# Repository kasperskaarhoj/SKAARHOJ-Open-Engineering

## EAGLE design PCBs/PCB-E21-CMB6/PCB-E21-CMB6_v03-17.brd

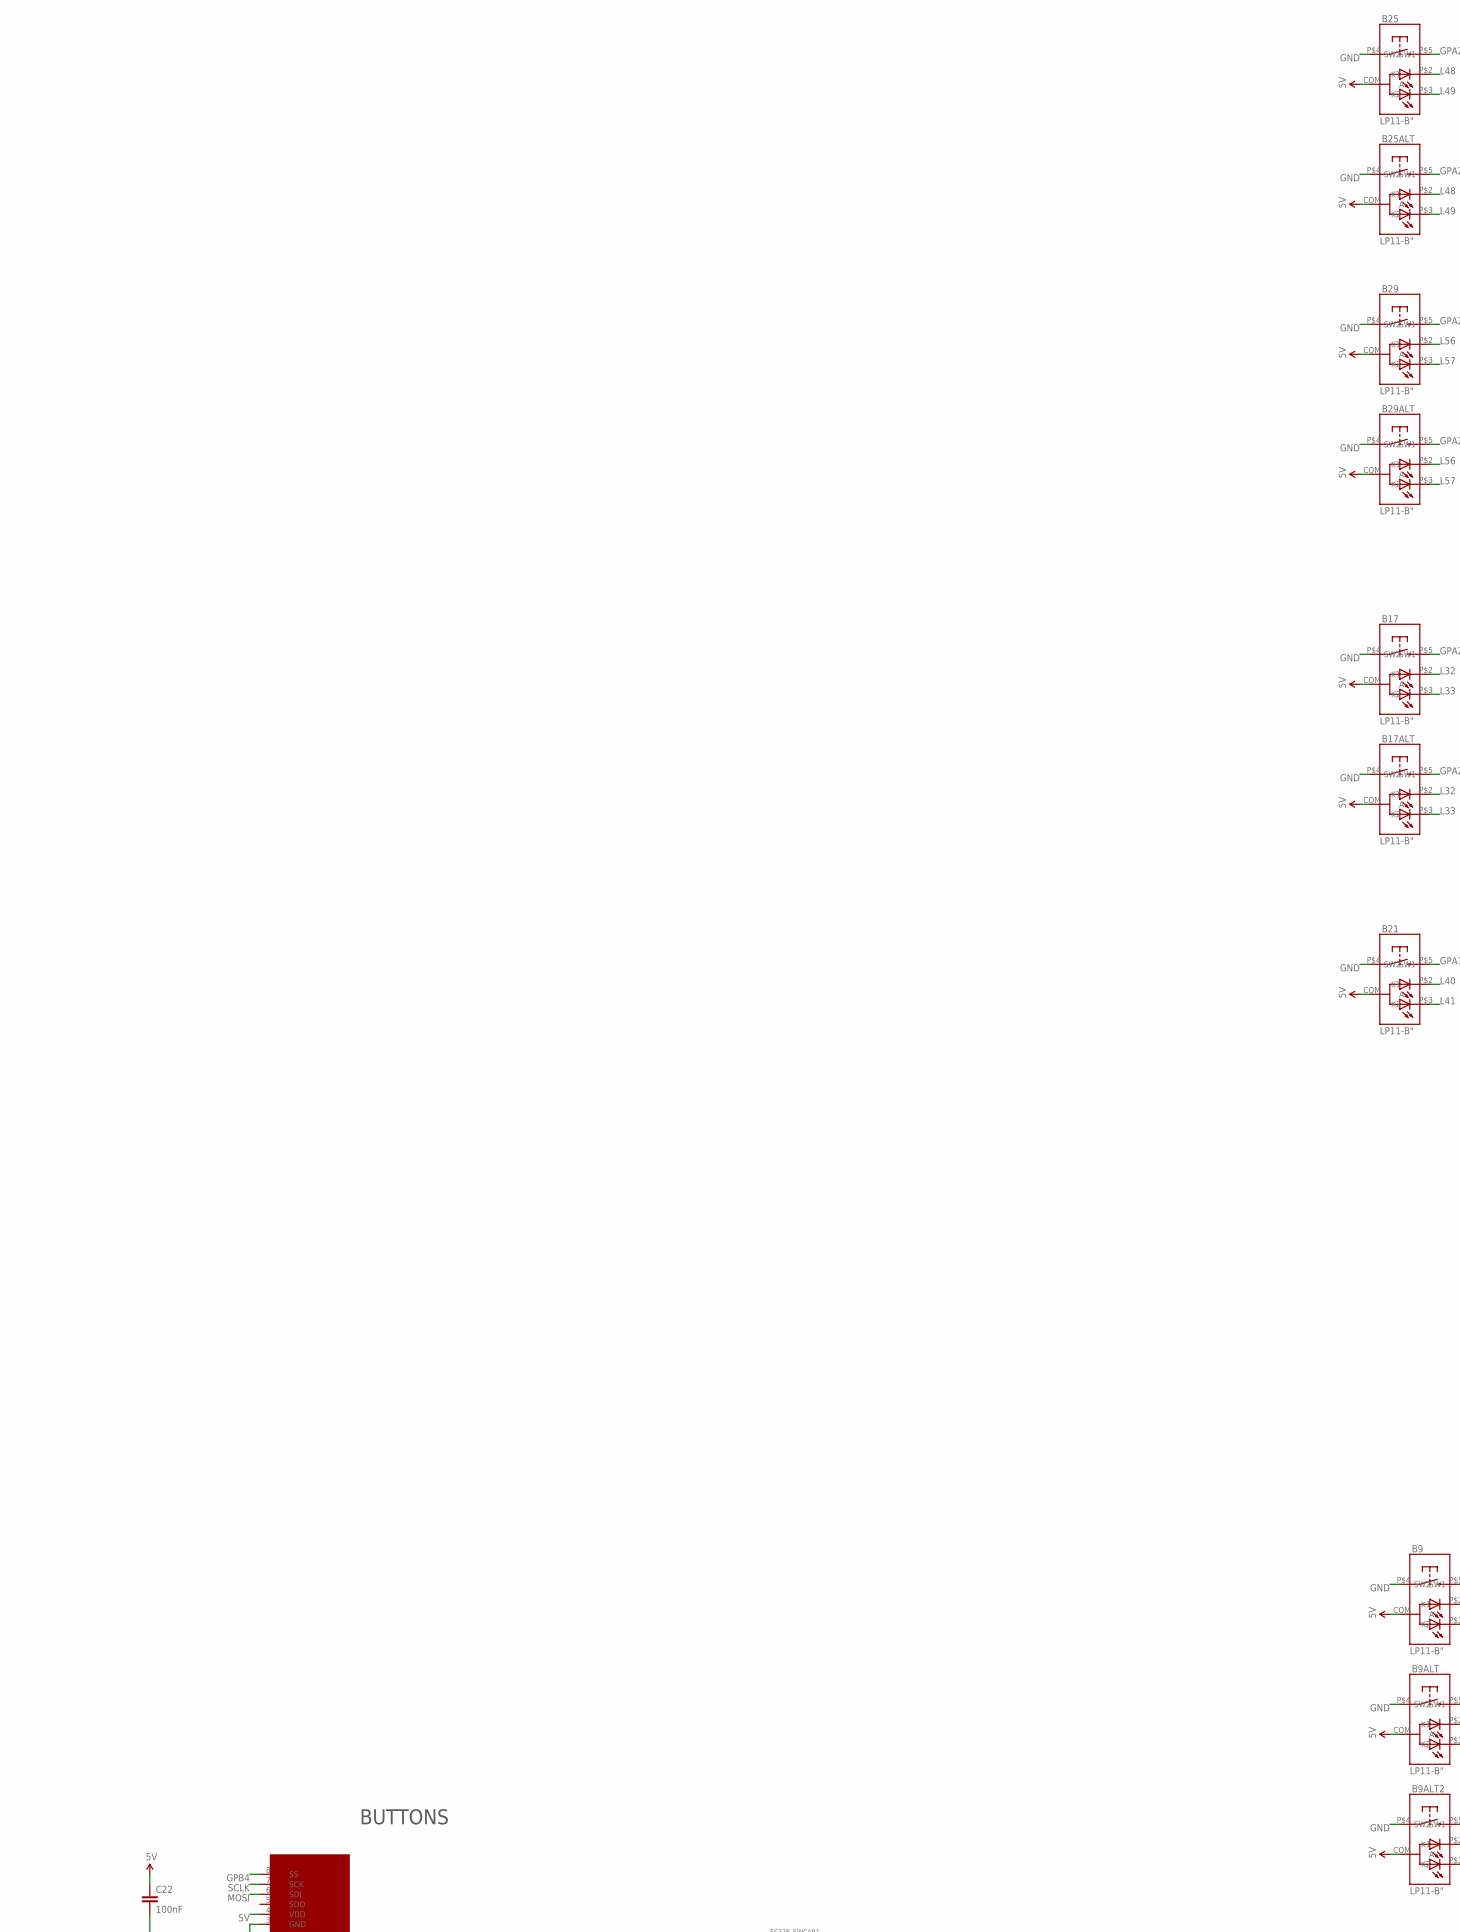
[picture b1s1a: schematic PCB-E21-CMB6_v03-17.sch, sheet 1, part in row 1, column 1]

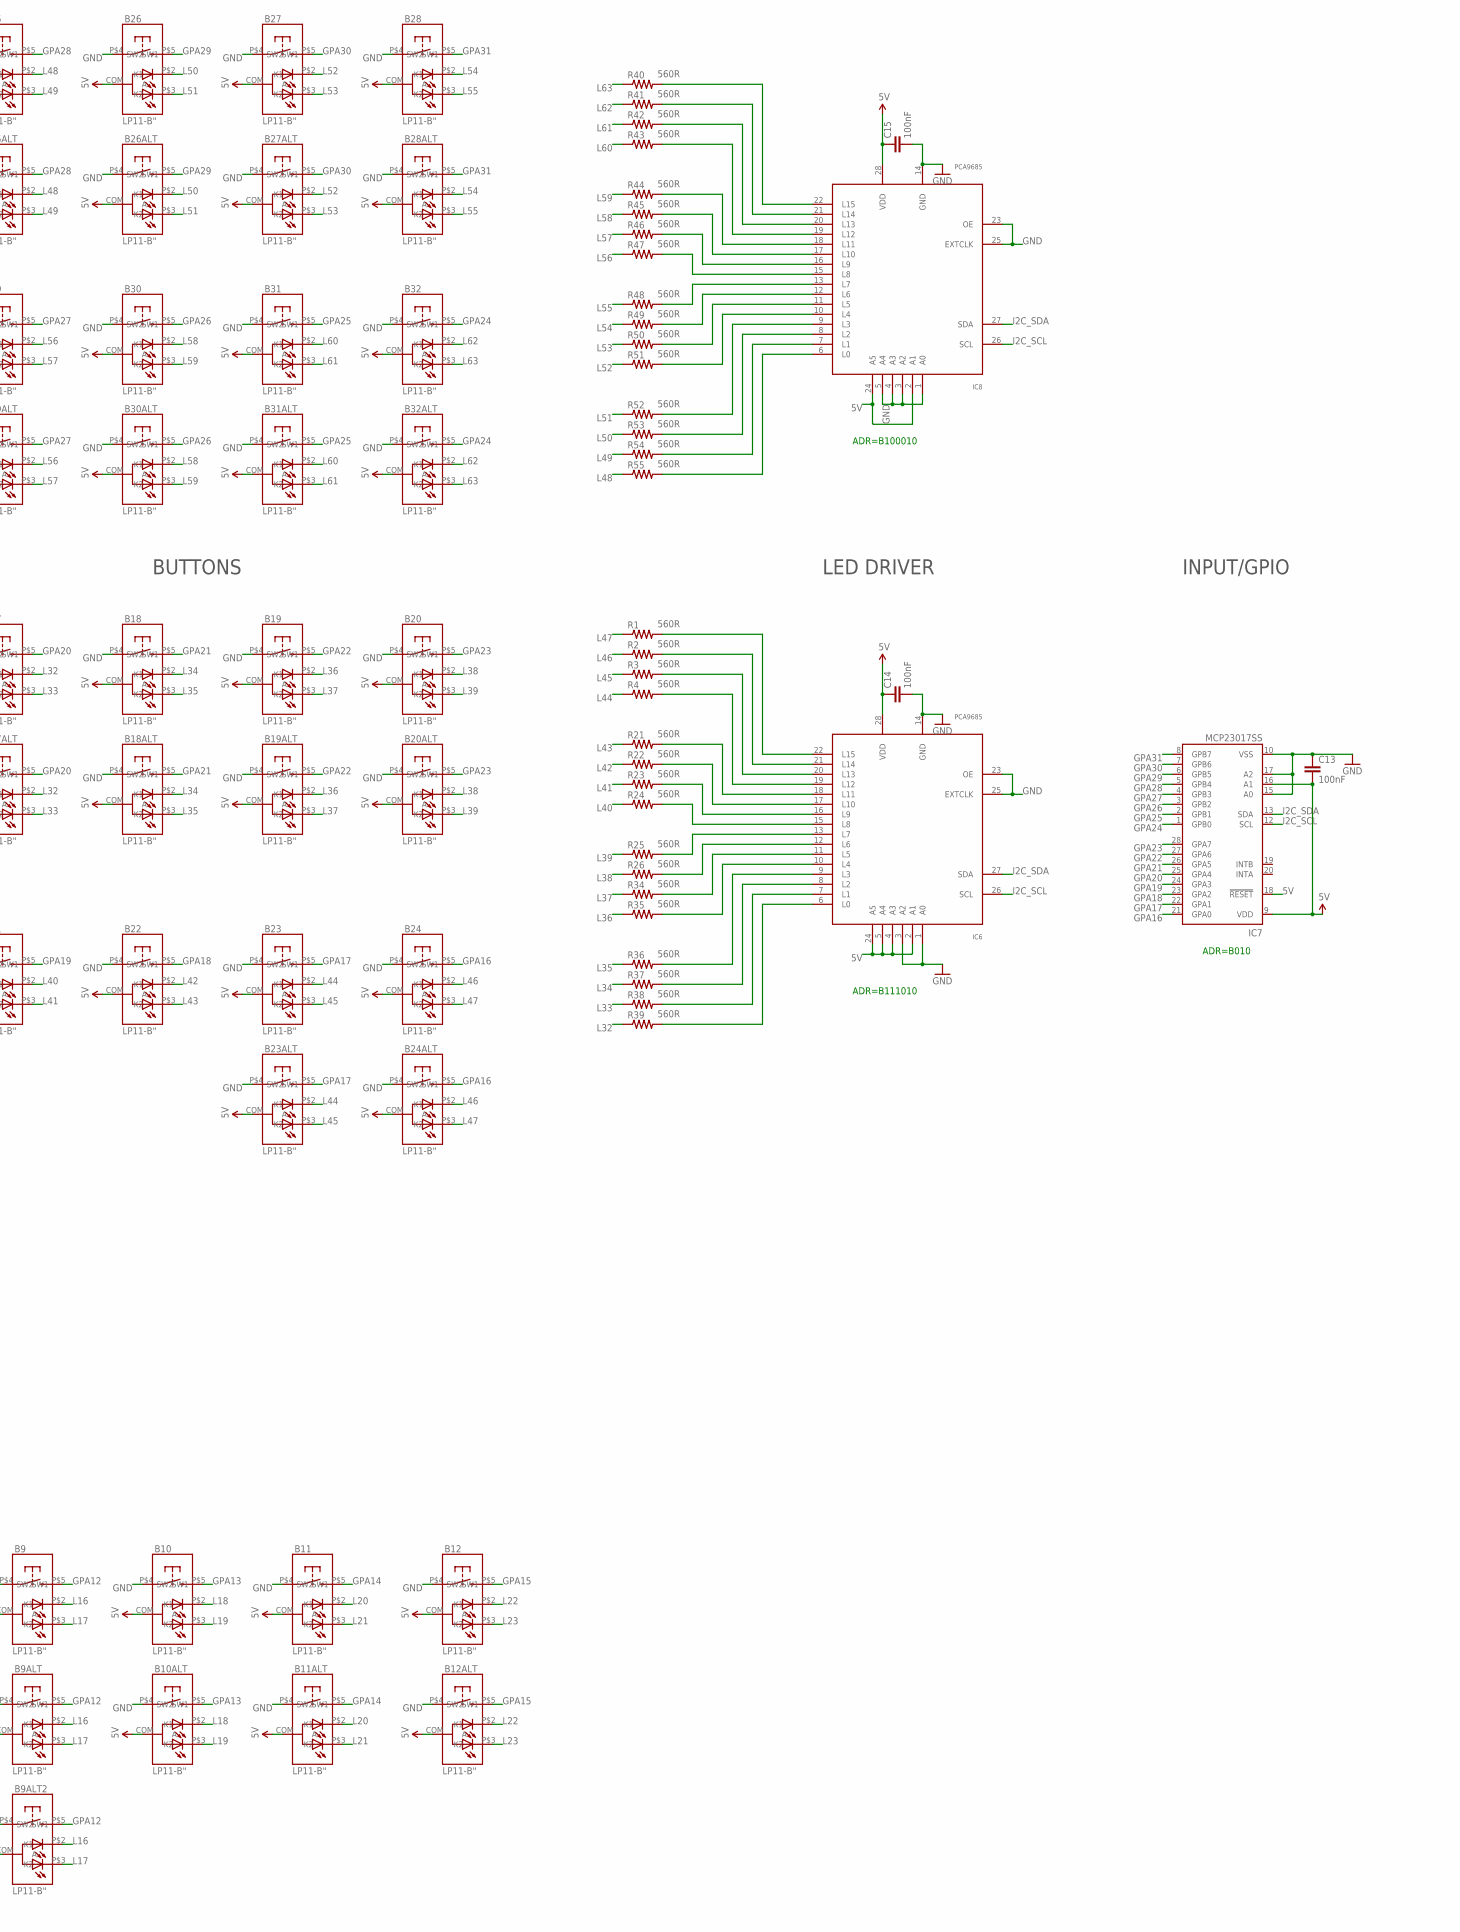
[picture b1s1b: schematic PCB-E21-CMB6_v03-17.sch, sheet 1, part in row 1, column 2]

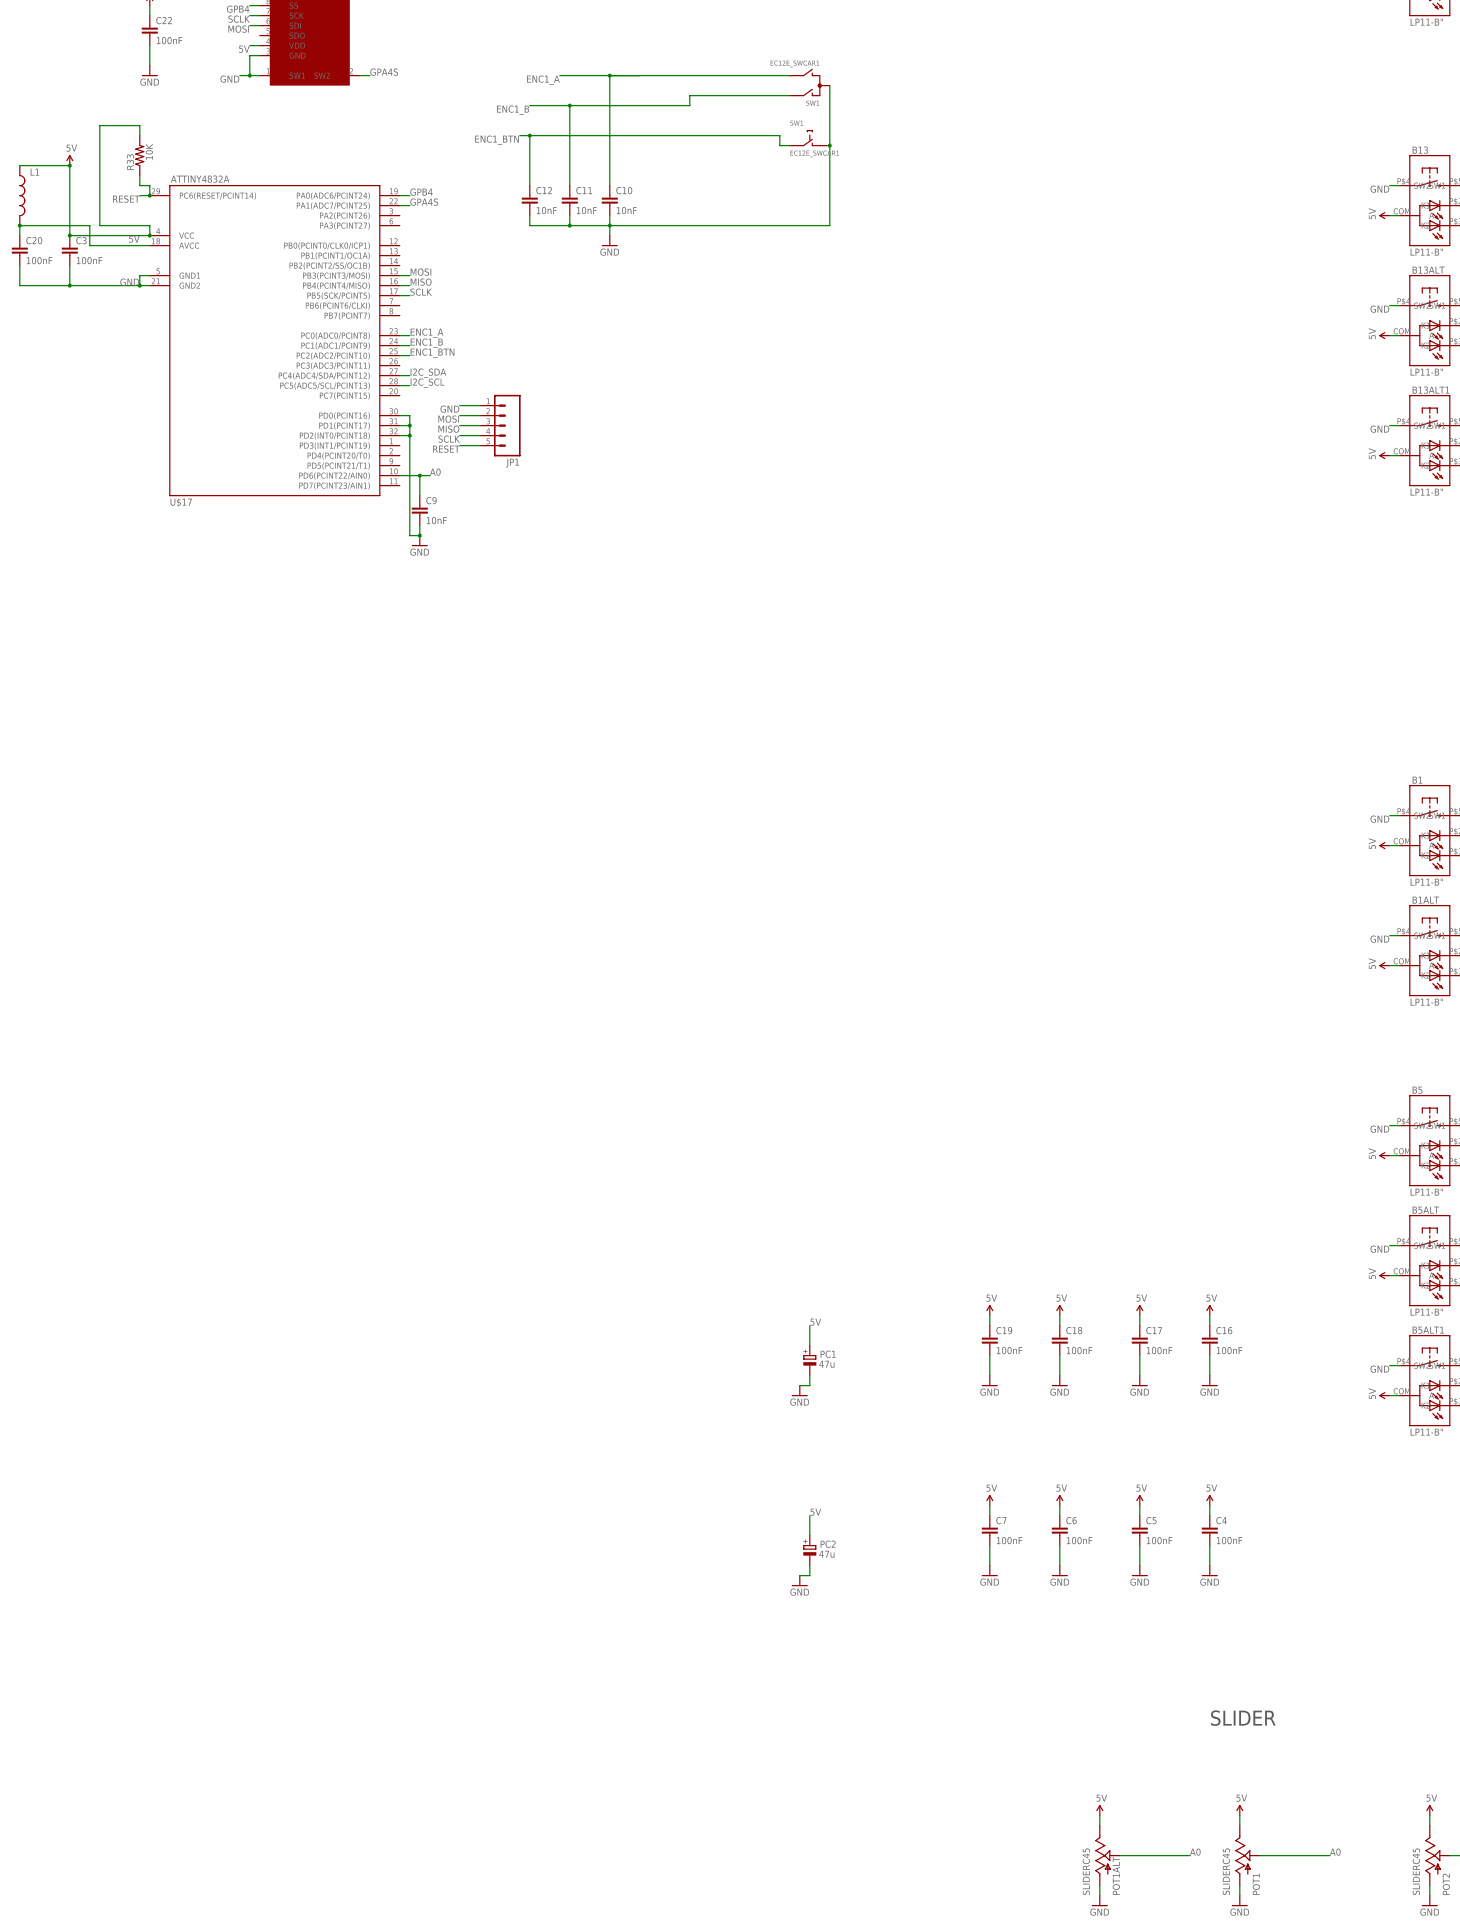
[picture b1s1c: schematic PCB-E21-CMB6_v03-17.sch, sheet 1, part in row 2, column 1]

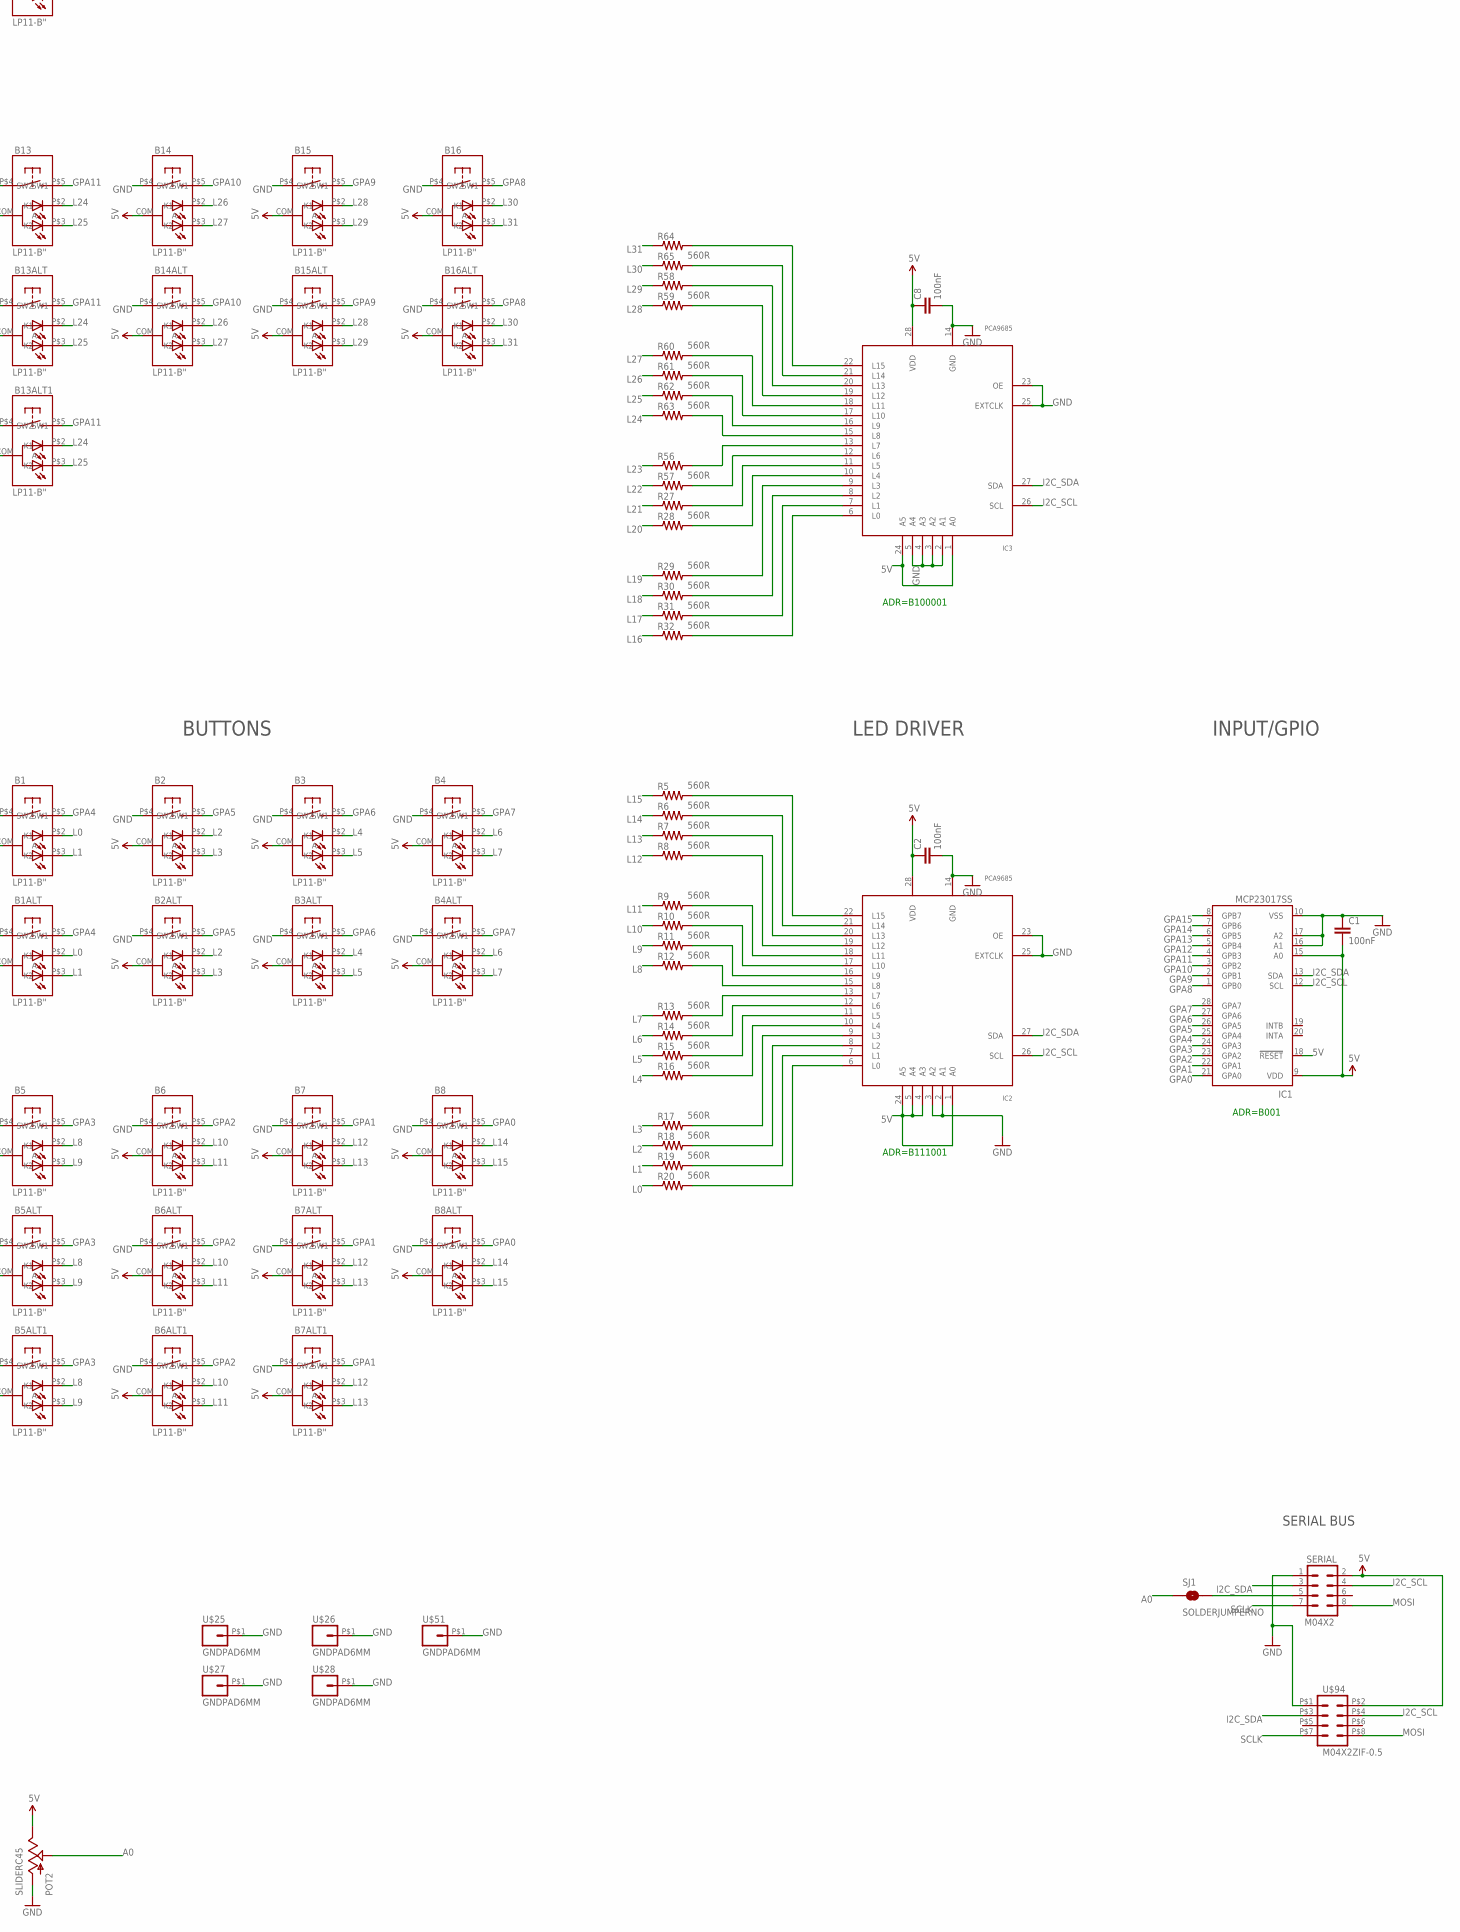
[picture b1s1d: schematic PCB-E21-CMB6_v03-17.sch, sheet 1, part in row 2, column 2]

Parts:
B1, B1ALT, B2, B2ALT, B3, B3ALT, B4, B4ALT, B5, B5ALT, B5ALT1, B6, B6ALT, B6ALT1, B7, B7ALT, B7ALT1, B8, B8ALT, B9, B9ALT, B9ALT2, B10, B10ALT, B11, B11ALT, B12, B12ALT, B13, B13ALT, B13ALT1, B14, B14ALT, B15, B15ALT, B16, B16ALT, B17, B17ALT, B18, B18ALT, B19, B19ALT, B20, B20ALT, B21, B22, B23, B23ALT, B24, B24ALT, B25, B25ALT, B26, B26ALT, B27, B27ALT, B28, B28ALT, B29, B29ALT, B30, B30ALT, B31, B31ALT, B32, B32ALT: LP11-B"; LP11
C1, C2, C3, C4, C5, C6, C7, C8, C13, C14, C15, C16, C17, C18, C19, C20, C22: 100nF; 0603-CAP
C9, C10, C11, C12: 10nF; 0603-CAP
IC1, IC7: MCP23017SS; SSOP28; MPN MCP23017-E/SS
IC2, IC3, IC6, IC8: PCA9685; TSSOP28
JP1: M051.27MM; 1X05-1.27MM
L1: INDUCTOR0805; 0805
PC1, PC2: 47u; PANASONIC_D
POT1, POT1ALT, POT2: SLIDERC45; SLIDER45-CAR1
R1, R2, R3, R4, R5, R6, R7, R8, R9, R10, R11, R12, R13, R14, R15, R16, R17, R18, R19, R20, R21, R22, R23, R24, R25, R26, R27, R28, R29, R30, R31, R32, R34, R35, R36, R37, R38, R39, R40, R41, R42, R43, R44, R45, R46, R47, R48, R49, R50, R51, R52, R53, R54, R55, R56, R57, R58, R59, R60, R61, R62, R63, R64, R65: 560R; 0603-RES
R33: 10K; 0603-RES
SERIAL: M04X2; 2X4
SJ1: SOLDERJUMPERNO; SJ_2S-NO
SSW1: SMART_SWITCHSMART_SWITCH_8PIN; SMART_SWITCH
SW1: EC12E_SWCAR1; ALPS_EC12E_SW-CAR1
U$17: ATTINY4832A; TQFP32-08
U$25, U$26, U$27, U$28, U$51: GNDPAD6MM; 3.2MMPAD6MM
U$94: M04X2ZIF-0.5; ZIP-8-0.5

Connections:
5V: B1.COM (A), B1ALT.COM (A), B2.COM (A), B2ALT.COM (A), B3.COM (A), B3ALT.COM (A), B4.COM (A), B4ALT.COM (A), B5.COM (A), B5ALT.COM (A), B5ALT1.COM (A), B6.COM (A), B6ALT.COM (A), B6ALT1.COM (A), B7.COM (A), B7ALT.COM (A), B7ALT1.COM (A), B8.COM (A), B8ALT.COM (A), B9.COM (A), B9ALT.COM (A), B9ALT2.COM (A), B10.COM (A), B10ALT.COM (A), B11.COM (A), B11ALT.COM (A), B12.COM (A), B12ALT.COM (A), B13.COM (A), B13ALT.COM (A), B13ALT1.COM (A), B14.COM (A), B14ALT.COM (A), B15.COM (A), B15ALT.COM (A), B16.COM (A), B16ALT.COM (A), B17.COM (A), B17ALT.COM (A), B18.COM (A), B18ALT.COM (A), B19.COM (A), B19ALT.COM (A), B20.COM (A), B20ALT.COM (A), B21.COM (A), B22.COM (A), B23.COM (A), B23ALT.COM (A), B24.COM (A), B24ALT.COM (A), B25.COM (A), B25ALT.COM (A), B26.COM (A), B26ALT.COM (A), B27.COM (A), B27ALT.COM (A), B28.COM (A), B28ALT.COM (A), B29.COM (A), B29ALT.COM (A), B30.COM (A), B30ALT.COM (A), B31.COM (A), B31ALT.COM (A), B32.COM (A), B32ALT.COM (A), C1.2, C2.1, C3.1, C4.1, C5.1, C6.1, C7.1, C8.1, C13.2, C14.1, C15.1, C16.1, C17.1, C18.1, C19.1, C22.1, IC1.9 (VDD), IC1.15 (A0), IC1.18 (!RESET), IC2.1 (A0), IC2.4 (A3), IC2.5 (A4), IC2.24 (A5), IC2.28 (VDD), IC3.1 (A0), IC3.24 (A5), IC3.28 (VDD), IC6.2 (A1), IC6.4 (A3), IC6.5 (A4), IC6.24 (A5), IC6.28 (VDD), IC7.9 (VDD), IC7.16 (A1), IC7.18 (!RESET), IC8.2 (A1), IC8.24 (A5), IC8.28 (VDD), L1.1, PC1.+, PC2.+, POT1.1 (E), POT1ALT.1 (E), POT2.1 (E), R33.2, SERIAL.2, SSW1.4 (VDD), U$17.4 (VCC), U$94.P$2 (2)
A0: C9.1, POT1.2A (S), POT1ALT.2A (S), POT2.2A (S), SJ1.1, U$17.10 (PD6(PCINT22/AIN0))
ENC1_A: C10.1, SW1.B, U$17.23 (PC0(ADC0/PCINT8))
ENC1_B: C11.1, SW1.A, U$17.24 (PC1(ADC1/PCINT9))
ENC1_BTN: C12.1, SW1.E (2), U$17.25 (PC2(ADC2/PCINT10))
GND: B1.P$4 (SW1), B1ALT.P$4 (SW1), B2.P$4 (SW1), B2ALT.P$4 (SW1), B3.P$4 (SW1), B3ALT.P$4 (SW1), B4.P$4 (SW1), B4ALT.P$4 (SW1), B5.P$4 (SW1), B5ALT.P$4 (SW1), B5ALT1.P$4 (SW1), B6.P$4 (SW1), B6ALT.P$4 (SW1), B6ALT1.P$4 (SW1), B7.P$4 (SW1), B7ALT.P$4 (SW1), B7ALT1.P$4 (SW1), B8.P$4 (SW1), B8ALT.P$4 (SW1), B9.P$4 (SW1), B9ALT.P$4 (SW1), B9ALT2.P$4 (SW1), B10.P$4 (SW1), B10ALT.P$4 (SW1), B11.P$4 (SW1), B11ALT.P$4 (SW1), B12.P$4 (SW1), B12ALT.P$4 (SW1), B13.P$4 (SW1), B13ALT.P$4 (SW1), B13ALT1.P$4 (SW1), B14.P$4 (SW1), B14ALT.P$4 (SW1), B15.P$4 (SW1), B15ALT.P$4 (SW1), B16.P$4 (SW1), B16ALT.P$4 (SW1), B17.P$4 (SW1), B17ALT.P$4 (SW1), B18.P$4 (SW1), B18ALT.P$4 (SW1), B19.P$4 (SW1), B19ALT.P$4 (SW1), B20.P$4 (SW1), B20ALT.P$4 (SW1), B21.P$4 (SW1), B22.P$4 (SW1), B23.P$4 (SW1), B23ALT.P$4 (SW1), B24.P$4 (SW1), B24ALT.P$4 (SW1), B25.P$4 (SW1), B25ALT.P$4 (SW1), B26.P$4 (SW1), B26ALT.P$4 (SW1), B27.P$4 (SW1), B27ALT.P$4 (SW1), B28.P$4 (SW1), B28ALT.P$4 (SW1), B29.P$4 (SW1), B29ALT.P$4 (SW1), B30.P$4 (SW1), B30ALT.P$4 (SW1), B31.P$4 (SW1), B31ALT.P$4 (SW1), B32.P$4 (SW1), B32ALT.P$4 (SW1), C1.1, C2.2, C3.2, C4.2, C5.2, C6.2, C7.2, C8.2, C9.2, C10.2, C11.2, C12.2, C13.1, C14.2, C15.2, C16.2, C17.2, C18.2, C19.2, C20.2, C22.2, IC1.10 (VSS), IC1.16 (A1), IC1.17 (A2), IC2.2 (A1), IC2.3 (A2), IC2.14 (GND), IC2.23 (OE), IC2.25 (EXTCLK), IC3.2 (A1), IC3.3 (A2), IC3.4 (A3), IC3.5 (A4), IC3.14 (GND), IC3.23 (OE), IC3.25 (EXTCLK), IC6.1 (A0), IC6.3 (A2), IC6.14 (GND), IC6.23 (OE), IC6.25 (EXTCLK), IC7.10 (VSS), IC7.15 (A0), IC7.17 (A2), IC8.1 (A0), IC8.3 (A2), IC8.4 (A3), IC8.5 (A4), IC8.14 (GND), IC8.23 (OE), IC8.25 (EXTCLK), JP1.1, PC1.-, PC2.-, POT1.3 (A), POT1ALT.3 (A), POT2.3 (A), SERIAL.1, SSW1.1 (SW1), SSW1.3 (GND), SW1.C, SW1.D (1), U$17.5 (GND1), U$17.21 (GND2), U$17.30 (PD0(PCINT16)), U$17.31 (PD1(PCINT17)), U$17.32 (PD2(INT0/PCINT18)), U$25.P$1, U$26.P$1, U$27.P$1, U$28.P$1, U$51.P$1, U$94.P$1 (1)
GPA0: B8.P$5 (SW2), B8ALT.P$5 (SW2), IC1.21 (GPA0)
GPA1: B7.P$5 (SW2), B7ALT.P$5 (SW2), B7ALT1.P$5 (SW2), IC1.22 (GPA1)
GPA2: B6.P$5 (SW2), B6ALT.P$5 (SW2), B6ALT1.P$5 (SW2), IC1.23 (GPA2)
GPA3: B5.P$5 (SW2), B5ALT.P$5 (SW2), B5ALT1.P$5 (SW2), IC1.24 (GPA3)
GPA4: B1.P$5 (SW2), B1ALT.P$5 (SW2), IC1.25 (GPA4)
GPA4S: SSW1.2 (SW2), U$17.22 (PA1(ADC7/PCINT25))
GPA5: B2.P$5 (SW2), B2ALT.P$5 (SW2), IC1.26 (GPA5)
GPA6: B3.P$5 (SW2), B3ALT.P$5 (SW2), IC1.27 (GPA6)
GPA7: B4.P$5 (SW2), B4ALT.P$5 (SW2), IC1.28 (GPA7)
GPA8: B16.P$5 (SW2), B16ALT.P$5 (SW2), IC1.1 (GPB0)
GPA9: B15.P$5 (SW2), B15ALT.P$5 (SW2), IC1.2 (GPB1)
GPA10: B14.P$5 (SW2), B14ALT.P$5 (SW2), IC1.3 (GPB2)
GPA11: B13.P$5 (SW2), B13ALT.P$5 (SW2), B13ALT1.P$5 (SW2), IC1.4 (GPB3)
GPA12: B9.P$5 (SW2), B9ALT.P$5 (SW2), B9ALT2.P$5 (SW2), IC1.5 (GPB4)
GPA13: B10.P$5 (SW2), B10ALT.P$5 (SW2), IC1.6 (GPB5)
GPA14: B11.P$5 (SW2), B11ALT.P$5 (SW2), IC1.7 (GPB6)
GPA15: B12.P$5 (SW2), B12ALT.P$5 (SW2), IC1.8 (GPB7)
GPA16: B24.P$5 (SW2), B24ALT.P$5 (SW2), IC7.21 (GPA0)
GPA17: B23.P$5 (SW2), B23ALT.P$5 (SW2), IC7.22 (GPA1)
GPA18: B22.P$5 (SW2), IC7.23 (GPA2)
GPA19: B21.P$5 (SW2), IC7.24 (GPA3)
GPA20: B17.P$5 (SW2), B17ALT.P$5 (SW2), IC7.25 (GPA4)
GPA21: B18.P$5 (SW2), B18ALT.P$5 (SW2), IC7.26 (GPA5)
GPA22: B19.P$5 (SW2), B19ALT.P$5 (SW2), IC7.27 (GPA6)
GPA23: B20.P$5 (SW2), B20ALT.P$5 (SW2), IC7.28 (GPA7)
GPA24: B32.P$5 (SW2), B32ALT.P$5 (SW2), IC7.1 (GPB0)
GPA25: B31.P$5 (SW2), B31ALT.P$5 (SW2), IC7.2 (GPB1)
GPA26: B30.P$5 (SW2), B30ALT.P$5 (SW2), IC7.3 (GPB2)
GPA27: B29.P$5 (SW2), B29ALT.P$5 (SW2), IC7.4 (GPB3)
GPA28: B25.P$5 (SW2), B25ALT.P$5 (SW2), IC7.5 (GPB4)
GPA29: B26.P$5 (SW2), B26ALT.P$5 (SW2), IC7.6 (GPB5)
GPA30: B27.P$5 (SW2), B27ALT.P$5 (SW2), IC7.7 (GPB6)
GPA31: B28.P$5 (SW2), B28ALT.P$5 (SW2), IC7.8 (GPB7)
GPB4: SSW1.8 (SS), U$17.19 (PA0(ADC6/PCINT24))
I2C_SCL: IC1.12 (SCL), IC2.26 (SCL), IC3.26 (SCL), IC6.26 (SCL), IC7.12 (SCL), IC8.26 (SCL), SERIAL.4, U$17.28 (PC5(ADC5/SCL/PCINT13)), U$94.P$4 (4)
I2C_SDA: IC1.13 (SDA), IC2.27 (SDA), IC3.27 (SDA), IC6.27 (SDA), IC7.13 (SDA), IC8.27 (SDA), SERIAL.3, U$17.27 (PC4(ADC4/SDA/PCINT12)), U$94.P$3 (3)
L0: B1.P$2 (K1), B1ALT.P$2 (K1), R20.1
L1: B1.P$3 (K2), B1ALT.P$3 (K2), R19.1
L2: B2.P$2 (K1), B2ALT.P$2 (K1), R18.1
L3: B2.P$3 (K2), B2ALT.P$3 (K2), R17.1
L4: B3.P$2 (K1), B3ALT.P$2 (K1), R16.1
L5: B3.P$3 (K2), B3ALT.P$3 (K2), R15.1
L6: B4.P$2 (K1), B4ALT.P$2 (K1), R14.1
L7: B4.P$3 (K2), B4ALT.P$3 (K2), R13.1
L8: B5.P$2 (K1), B5ALT.P$2 (K1), B5ALT1.P$2 (K1), R12.1
L9: B5.P$3 (K2), B5ALT.P$3 (K2), B5ALT1.P$3 (K2), R11.1
L10: B6.P$2 (K1), B6ALT.P$2 (K1), B6ALT1.P$2 (K1), R10.1
L11: B6.P$3 (K2), B6ALT.P$3 (K2), B6ALT1.P$3 (K2), R9.1
L12: B7.P$2 (K1), B7ALT.P$2 (K1), B7ALT1.P$2 (K1), R8.1
L13: B7.P$3 (K2), B7ALT.P$3 (K2), B7ALT1.P$3 (K2), R7.1
L14: B8.P$2 (K1), B8ALT.P$2 (K1), R6.1
L15: B8.P$3 (K2), B8ALT.P$3 (K2), R5.1
L16: B9.P$2 (K1), B9ALT.P$2 (K1), B9ALT2.P$2 (K1), R32.1
L17: B9.P$3 (K2), B9ALT.P$3 (K2), B9ALT2.P$3 (K2), R31.1
L18: B10.P$2 (K1), B10ALT.P$2 (K1), R30.1
L19: B10.P$3 (K2), B10ALT.P$3 (K2), R29.1
L20: B11.P$2 (K1), B11ALT.P$2 (K1), R28.1
L21: B11.P$3 (K2), B11ALT.P$3 (K2), R27.1
L22: B12.P$2 (K1), B12ALT.P$2 (K1), R57.1
L23: B12.P$3 (K2), B12ALT.P$3 (K2), R56.1
L24: B13.P$2 (K1), B13ALT.P$2 (K1), B13ALT1.P$2 (K1), R63.1
L25: B13.P$3 (K2), B13ALT.P$3 (K2), B13ALT1.P$3 (K2), R62.1
L26: B14.P$2 (K1), B14ALT.P$2 (K1), R61.1
L27: B14.P$3 (K2), B14ALT.P$3 (K2), R60.1
L28: B15.P$2 (K1), B15ALT.P$2 (K1), R59.1
L29: B15.P$3 (K2), B15ALT.P$3 (K2), R58.1
L30: B16.P$2 (K1), B16ALT.P$2 (K1), R65.1
L31: B16.P$3 (K2), B16ALT.P$3 (K2), R64.1
L32: B17.P$2 (K1), B17ALT.P$2 (K1), R39.1
L33: B17.P$3 (K2), B17ALT.P$3 (K2), R38.1
L34: B18.P$2 (K1), B18ALT.P$2 (K1), R37.1
L35: B18.P$3 (K2), B18ALT.P$3 (K2), R36.1
L36: B19.P$2 (K1), B19ALT.P$2 (K1), R35.1
L37: B19.P$3 (K2), B19ALT.P$3 (K2), R34.1
L38: B20.P$2 (K1), B20ALT.P$2 (K1), R26.1
L39: B20.P$3 (K2), B20ALT.P$3 (K2), R25.1
L40: B21.P$2 (K1), R24.1
L41: B21.P$3 (K2), R23.1
L42: B22.P$2 (K1), R22.1
L43: B22.P$3 (K2), R21.1
L44: B23.P$2 (K1), B23ALT.P$2 (K1), R4.1
L45: B23.P$3 (K2), B23ALT.P$3 (K2), R3.1
L46: B24.P$2 (K1), B24ALT.P$2 (K1), R2.1
L47: B24.P$3 (K2), B24ALT.P$3 (K2), R1.1
L48: B25.P$2 (K1), B25ALT.P$2 (K1), R55.1
L49: B25.P$3 (K2), B25ALT.P$3 (K2), R54.1
L50: B26.P$2 (K1), B26ALT.P$2 (K1), R53.1
L51: B26.P$3 (K2), B26ALT.P$3 (K2), R52.1
L52: B27.P$2 (K1), B27ALT.P$2 (K1), R51.1
L53: B27.P$3 (K2), B27ALT.P$3 (K2), R50.1
L54: B28.P$2 (K1), B28ALT.P$2 (K1), R49.1
L55: B28.P$3 (K2), B28ALT.P$3 (K2), R48.1
L56: B29.P$2 (K1), B29ALT.P$2 (K1), R47.1
L57: B29.P$3 (K2), B29ALT.P$3 (K2), R46.1
L58: B30.P$2 (K1), B30ALT.P$2 (K1), R45.1
L59: B30.P$3 (K2), B30ALT.P$3 (K2), R44.1
L60: B31.P$2 (K1), B31ALT.P$2 (K1), R43.1
L61: B31.P$3 (K2), B31ALT.P$3 (K2), R42.1
L62: B32.P$2 (K1), B32ALT.P$2 (K1), R41.1
L63: B32.P$3 (K2), B32ALT.P$3 (K2), R40.1
MISO: JP1.3, U$17.16 (PB4(PCINT4/MISO))
MOSI: JP1.2, SERIAL.8, SSW1.6 (SDI), U$17.15 (PB3(PCINT3/MOSI)), U$94.P$8 (8)
unnamed: SERIAL.5, SJ1.2
unnamed: IC6.13 (L7), R25.2
unnamed: IC3.11 (L5), R27.2
unnamed: IC2.13 (L7), R13.2
unnamed: IC2.12 (L6), R14.2
unnamed: IC3.10 (L4), R28.2
unnamed: IC2.11 (L5), R15.2
unnamed: IC3.9 (L3), R29.2
unnamed: IC2.10 (L4), R16.2
unnamed: IC2.9 (L3), R17.2
unnamed: IC2.8 (L2), R18.2
unnamed: IC2.7 (L1), R19.2
unnamed: IC3.8 (L2), R30.2
unnamed: IC3.7 (L1), R31.2
unnamed: IC3.6 (L0), R32.2
unnamed: IC6.12 (L6), R26.2
unnamed: IC6.11 (L5), R34.2
unnamed: IC6.10 (L4), R35.2
unnamed: IC2.6 (L0), R20.2
unnamed: IC2.15 (L8), R12.2
unnamed: IC2.16 (L9), R11.2
unnamed: IC2.17 (L10), R10.2
unnamed: IC2.18 (L11), R9.2
unnamed: IC2.19 (L12), R8.2
unnamed: IC2.20 (L13), R7.2
unnamed: IC2.21 (L14), R6.2
unnamed: IC2.22 (L15), R5.2
unnamed: IC6.9 (L3), R36.2
unnamed: IC6.8 (L2), R37.2
unnamed: IC6.7 (L1), R38.2
unnamed: IC6.6 (L0), R39.2
unnamed: IC6.15 (L8), R24.2
unnamed: C20.1, L1.2, U$17.18 (AVCC)
unnamed: IC6.16 (L9), R23.2
unnamed: IC6.17 (L10), R22.2
unnamed: IC6.18 (L11), R21.2
unnamed: IC6.19 (L12), R4.2
unnamed: IC6.20 (L13), R3.2
unnamed: IC6.21 (L14), R2.2
unnamed: IC6.22 (L15), R1.2
unnamed: IC8.13 (L7), R48.2
unnamed: IC8.12 (L6), R49.2
unnamed: IC8.11 (L5), R50.2
unnamed: IC8.10 (L4), R51.2
unnamed: IC8.9 (L3), R52.2
unnamed: IC8.8 (L2), R53.2
unnamed: IC8.7 (L1), R54.2
unnamed: IC8.6 (L0), R55.2
unnamed: IC8.15 (L8), R47.2
unnamed: IC8.16 (L9), R46.2
unnamed: IC8.17 (L10), R45.2
unnamed: IC8.18 (L11), R44.2
unnamed: IC8.19 (L12), R43.2
unnamed: IC8.20 (L13), R42.2
unnamed: IC8.21 (L14), R41.2
unnamed: IC8.22 (L15), R40.2
unnamed: IC3.12 (L6), R57.2
unnamed: IC3.13 (L7), R56.2
unnamed: IC3.15 (L8), R63.2
unnamed: IC3.16 (L9), R62.2
unnamed: IC3.17 (L10), R61.2
unnamed: IC3.18 (L11), R60.2
unnamed: IC3.19 (L12), R59.2
unnamed: IC3.20 (L13), R58.2
unnamed: IC3.21 (L14), R65.2
unnamed: IC3.22 (L15), R64.2
RESET: JP1.5, R33.1, U$17.29 (PC6(RESET/PCINT14))
SCLK: JP1.4, SERIAL.7, SSW1.7 (SCK), U$17.17 (PB5(SCK/PCINT5)), U$94.P$7 (7)

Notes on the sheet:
SERIAL BUS
SLIDER
BUTTONS
ADR=B111001
ADR=B001
LED DRIVER
INPUT/GPIO
ADR=B100001
ADR=B111010
ADR=B010
ADR=B100010

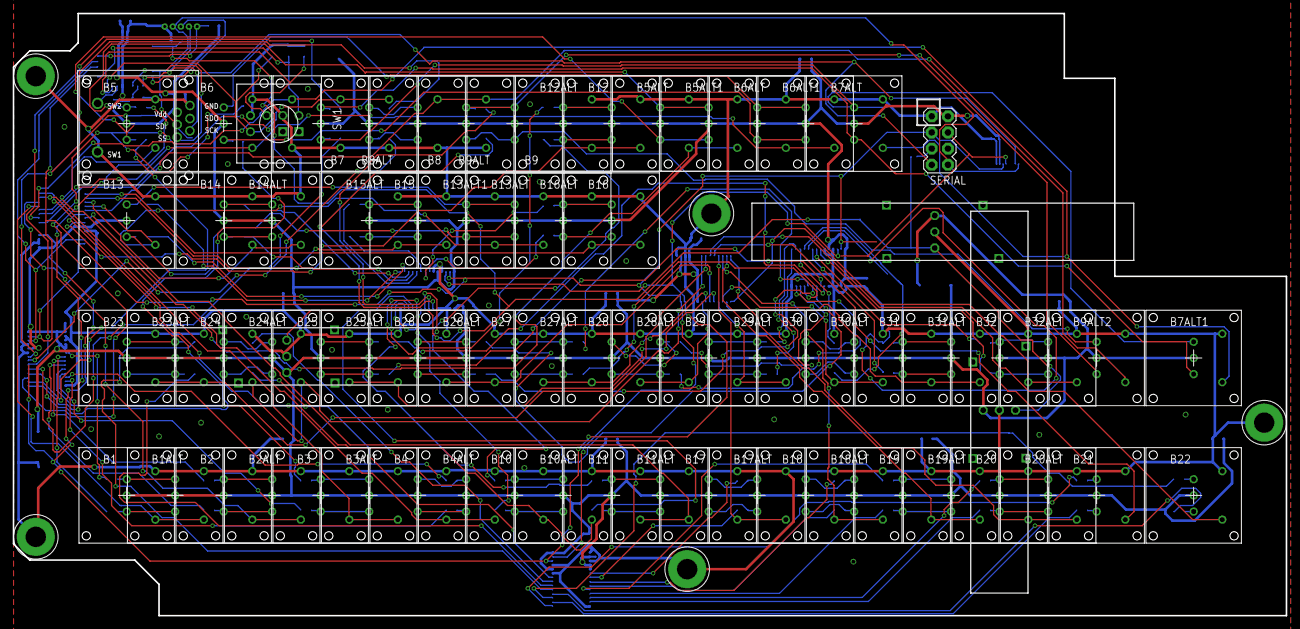
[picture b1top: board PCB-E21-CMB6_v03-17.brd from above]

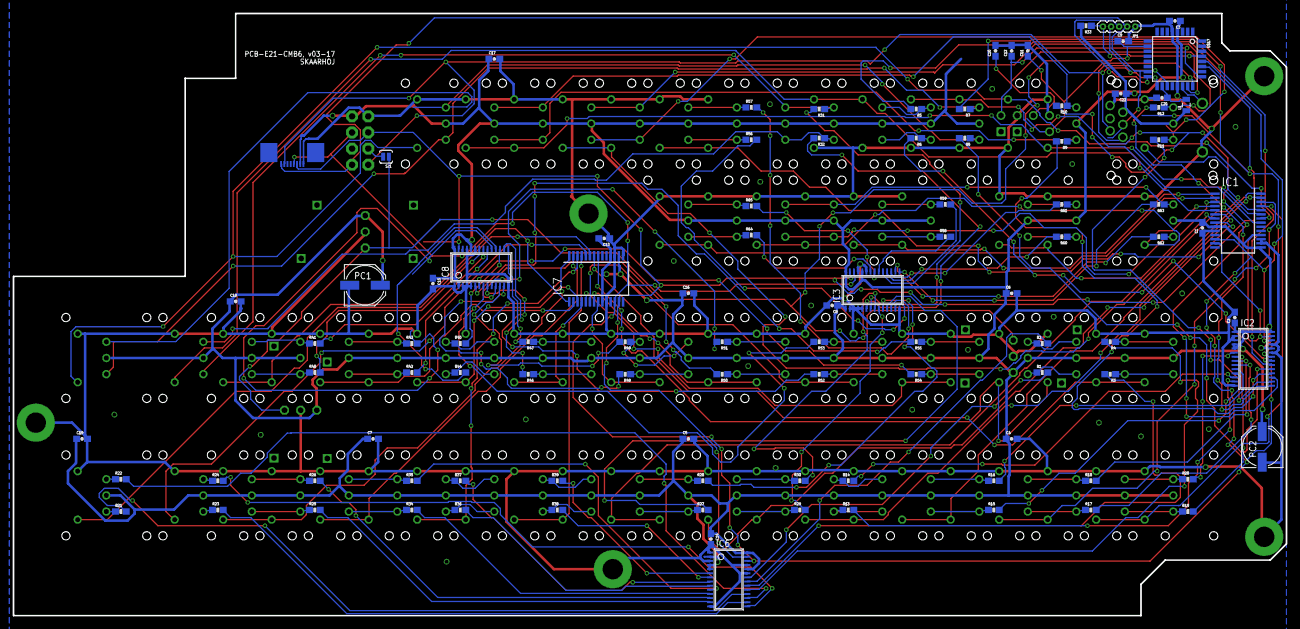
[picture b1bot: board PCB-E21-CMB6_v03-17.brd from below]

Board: 2 copper layers, 200.0 x 94.6 mm, 177 parts (99 on the bottom side), 176 nets.

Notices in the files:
parts and their libraries:
SparkFun: Licensing: CC v3.0 Share-Alike You are welcome to use this library for commercial purposes.
